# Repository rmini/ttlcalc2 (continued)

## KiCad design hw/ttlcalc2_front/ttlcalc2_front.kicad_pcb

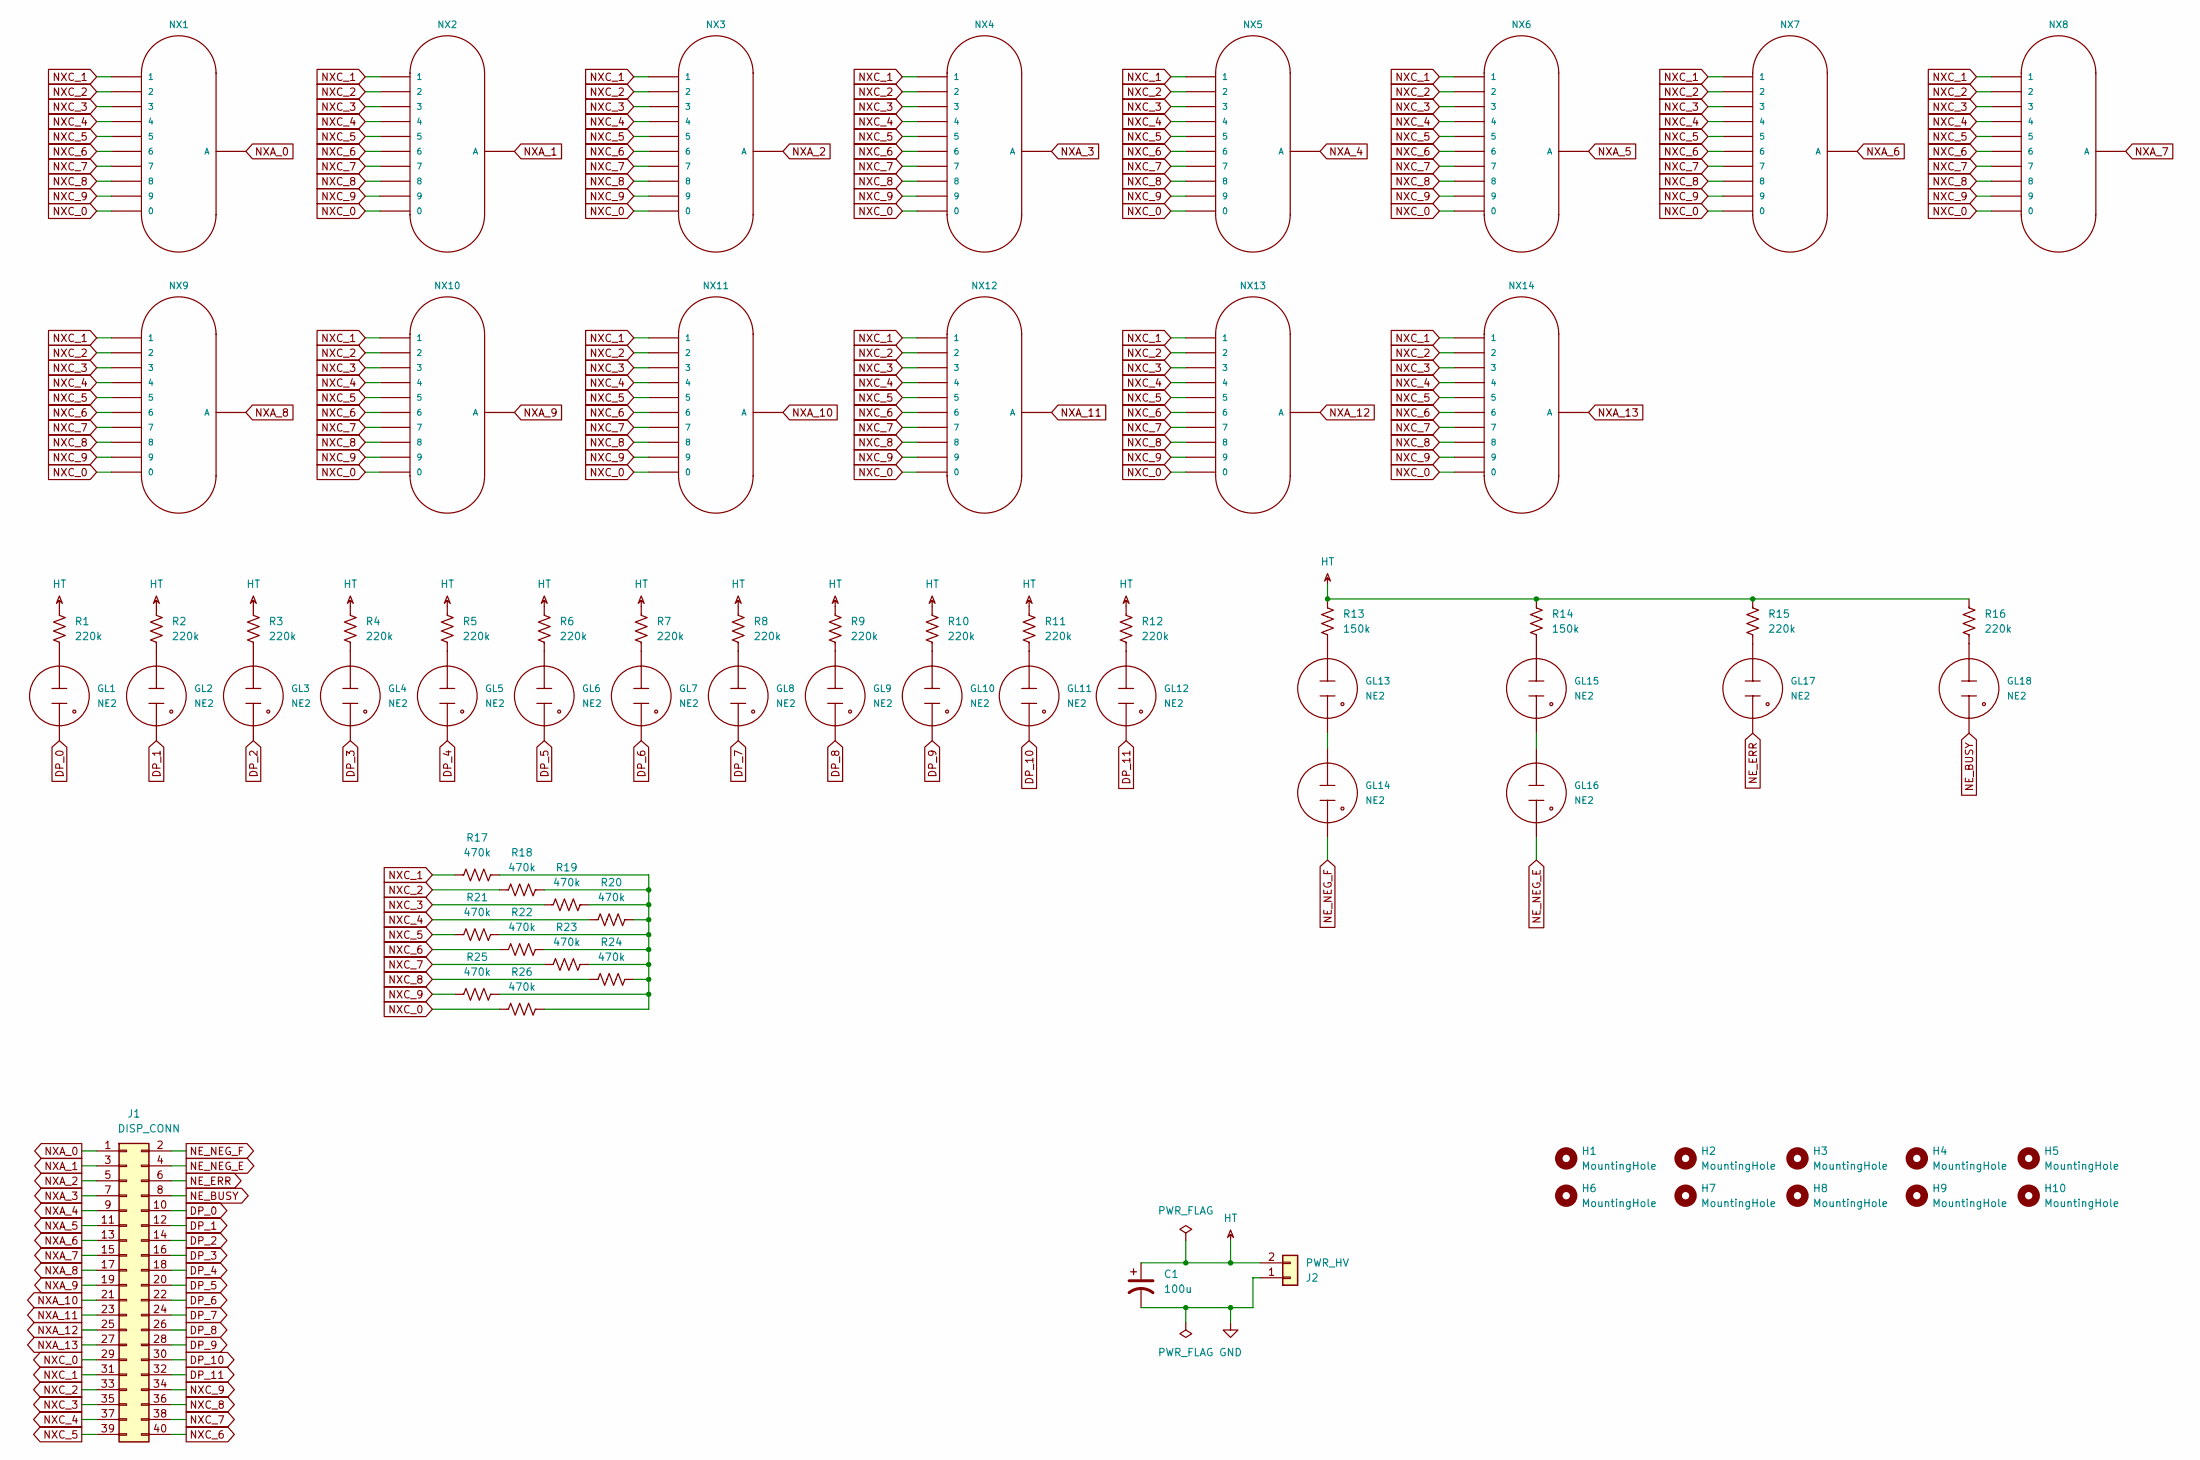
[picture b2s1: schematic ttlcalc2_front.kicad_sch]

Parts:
C1: 100u; CP_Radial_D18.0mm_P7.50mm
GL1, GL2, GL3, GL4, GL5, GL6, GL7, GL8, GL9, GL10, GL11, GL12, GL13, GL14, GL15, GL16, GL17, GL18: NE2; mynixies-NE2-NEON-BULB-DRILL
H1, H2, H3, H4, H5, H6, H7, H8, H9, H10: MountingHole; MountingHole_3.2mm_M3
J1: DISP_CONN; IDC-Header_2x20_P2.54mm_Vertical
J2: PWR_HV; TerminalBlock_Phoenix_MKDS-1,5-2-5.08_1x02_P5.08mm_Horizont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
NX1, NX2, NX3, NX4, NX5, NX6, NX7, NX8, NX9, NX10, NX11, NX12, NX13, NX14: IN-12A; nixies-us-IN-12-DSUB-NOHOLE
R1, R2, R3, R4, R5, R6, R7, R8, R9, R10, R11, R12, R15, R16: 220k; R_Axial_DIN0207_L6.3mm_D2.5mm_P7.62mm_Horizontal
R13, R14: 150k; R_Axial_DIN0207_L6.3mm_D2.5mm_P7.62mm_Horizontal
R17, R18, R19, R20, R21, R22, R23, R24, R25, R26: 470k; R_Axial_DIN0207_L6.3mm_D2.5mm_P7.62mm_Horizontal

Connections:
DP_0: GL1.2 (A1), J1.10
DP_1: GL2.2 (A1), J1.12
DP_2: GL3.2 (A1), J1.14
DP_3: GL4.2 (A1), J1.16
DP_4: GL5.2 (A1), J1.18
DP_5: GL6.2 (A1), J1.20
DP_6: GL7.2 (A1), J1.22
DP_7: GL8.2 (A1), J1.24
DP_8: GL9.2 (A1), J1.26
DP_9: GL10.2 (A1), J1.28
DP_10: GL11.2 (A1), J1.30
DP_11: GL12.2 (A1), J1.32
GND: C1.2, J2.1
HT: C1.1, J2.2, R1.1, R2.1, R3.1, R4.1, R5.1, R6.1, R7.1, R8.1, R9.1, R10.1, R11.1, R12.1, R13.1, R14.1, R15.1, R16.1
NE_BUSY: GL18.2 (A1), J1.8
NE_ERR: GL17.2 (A1), J1.6
NE_NEG_E: GL16.2 (A1), J1.4
NE_NEG_F: GL14.2 (A1), J1.2
NXA_0: J1.1, NX1.A
NXA_1: J1.3, NX2.A
NXA_2: J1.5, NX3.A
NXA_3: J1.7, NX4.A
NXA_4: J1.9, NX5.A
NXA_5: J1.11, NX6.A
NXA_6: J1.13, NX7.A
NXA_7: J1.15, NX8.A
NXA_8: J1.17, NX9.A
NXA_9: J1.19, NX10.A
NXA_10: J1.21, NX11.A
NXA_11: J1.23, NX12.A
NXA_12: J1.25, NX13.A
NXA_13: J1.27, NX14.A
NXC_0: J1.29, NX1.0, NX2.0, NX3.0, NX4.0, NX5.0, NX6.0, NX7.0, NX8.0, NX9.0, NX10.0, NX11.0, NX12.0, NX13.0, NX14.0, R26.1
NXC_1: J1.31, NX1.1, NX2.1, NX3.1, NX4.1, NX5.1, NX6.1, NX7.1, NX8.1, NX9.1, NX10.1, NX11.1, NX12.1, NX13.1, NX14.1, R17.1
NXC_2: J1.33, NX1.2, NX2.2, NX3.2, NX4.2, NX5.2, NX6.2, NX7.2, NX8.2, NX9.2, NX10.2, NX11.2, NX12.2, NX13.2, NX14.2, R18.1
NXC_3: J1.35, NX1.3, NX2.3, NX3.3, NX4.3, NX5.3, NX6.3, NX7.3, NX8.3, NX9.3, NX10.3, NX11.3, NX12.3, NX13.3, NX14.3, R19.1
NXC_4: J1.37, NX1.4, NX2.4, NX3.4, NX4.4, NX5.4, NX6.4, NX7.4, NX8.4, NX9.4, NX10.4, NX11.4, NX12.4, NX13.4, NX14.4, R20.1
NXC_5: J1.39, NX1.5, NX2.5, NX3.5, NX4.5, NX5.5, NX6.5, NX7.5, NX8.5, NX9.5, NX10.5, NX11.5, NX12.5, NX13.5, NX14.5, R21.1
NXC_6: J1.40, NX1.6, NX2.6, NX3.6, NX4.6, NX5.6, NX6.6, NX7.6, NX8.6, NX9.6, NX10.6, NX11.6, NX12.6, NX13.6, NX14.6, R22.1
NXC_7: J1.38, NX1.7, NX2.7, NX3.7, NX4.7, NX5.7, NX6.7, NX7.7, NX8.7, NX9.7, NX10.7, NX11.7, NX12.7, NX13.7, NX14.7, R23.1
NXC_8: J1.36, NX1.8, NX2.8, NX3.8, NX4.8, NX5.8, NX6.8, NX7.8, NX8.8, NX9.8, NX10.8, NX11.8, NX12.8, NX13.8, NX14.8, R24.1
NXC_9: J1.34, NX1.9, NX2.9, NX3.9, NX4.9, NX5.9, NX6.9, NX7.9, NX8.9, NX9.9, NX10.9, NX11.9, NX12.9, NX13.9, NX14.9, R25.1
unnamed: GL1.1 (A), R1.2
unnamed: GL2.1 (A), R2.2
unnamed: GL3.1 (A), R3.2
unnamed: GL4.1 (A), R4.2
unnamed: GL5.1 (A), R5.2
unnamed: GL6.1 (A), R6.2
unnamed: GL7.1 (A), R7.2
unnamed: GL8.1 (A), R8.2
unnamed: GL9.1 (A), R9.2
unnamed: GL10.1 (A), R10.2
unnamed: GL11.1 (A), R11.2
unnamed: GL12.1 (A), R12.2
unnamed: GL13.2 (A1), GL14.1 (A)
unnamed: GL13.1 (A), R13.2
unnamed: GL15.2 (A1), GL16.1 (A)
unnamed: GL15.1 (A), R14.2
unnamed: GL17.1 (A), R15.2
unnamed: GL18.1 (A), R16.2
unnamed: R17.2, R18.2, R19.2, R20.2, R21.2, R22.2, R23.2, R24.2, R25.2, R26.2

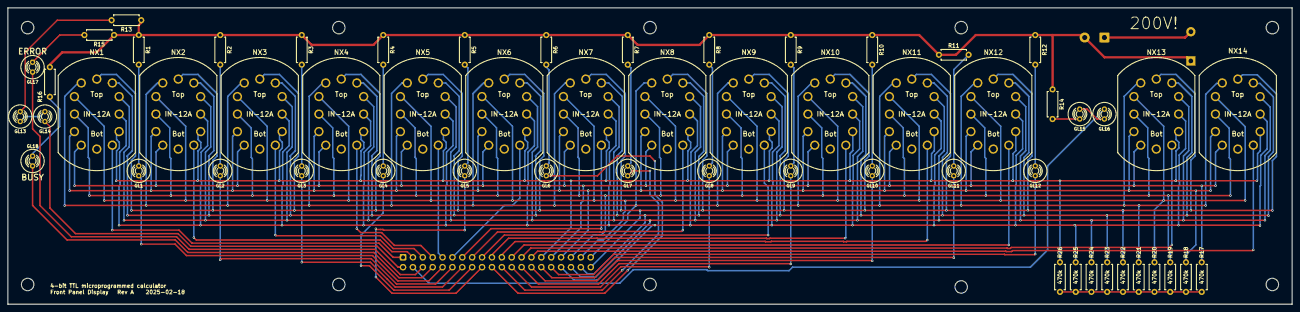
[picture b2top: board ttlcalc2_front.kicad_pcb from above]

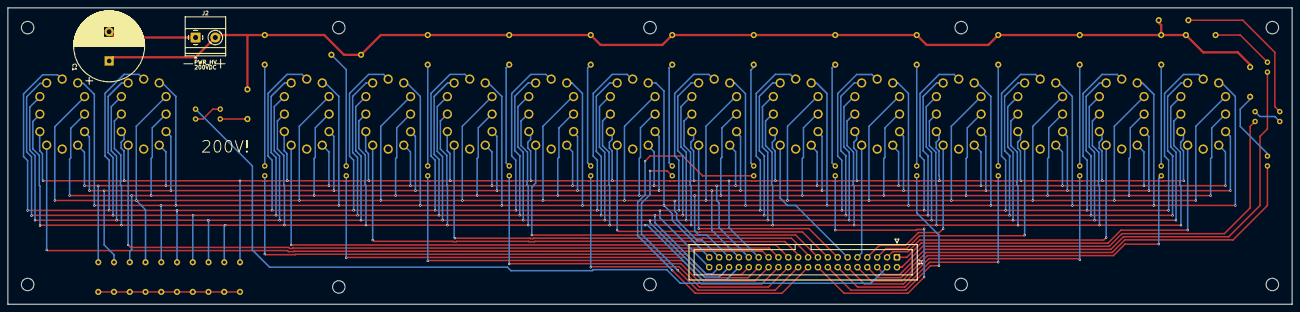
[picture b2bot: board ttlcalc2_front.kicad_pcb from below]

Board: 2 copper layers, 330.2 x 76.2 mm, 71 parts (3 on the bottom side), 61 nets.

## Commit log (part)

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2025-02-13 PCB cleanup
    Swap location of I/O output register and address latch
    Clean up routing
    Via stitch around clock traces
    Fill out sheet description block
2025-02-13 Moved logic board files into subdirectory
2025-02-13 Add in-progress display schematic
2025-02-14 Memory and I/O timing improvements
    Changed memory /WE to use combination of /CLK2 and /WMem to ensure /WE is de-asserted well before memory address becomes invalid
    Removed memory data input register, made unnecessary by above change
    Changed I/O output register to buffer (same reasons above)
    Fixed and updated date on PCB silkscreen
2025-02-15 Continue work on display driver board schematic
2025-02-16 Simplify display driver board, add busy light
    Removed digit storage and multiplexing logic from display driver, will handle in software instead
    Add driver for busy indicator
2025-02-16 Minor simplifications and ERC fix
    Fix missing NE_BUSY from bus definition
    Switch 74LS139 to 74LS138
    Remove extra bypass caps
2025-02-18 Display driver board routing and silkscreen tweaks
2025-02-18 Display driver geographical reannotate
2025-02-19 Commit front panel display board schematic and PCB
2025-02-19 Minor routing tweaks to front panel display
2025-02-24 Convert to KiCad 9.0
    Convert to KiCad 9.0 format
    Tweak silkscreen to fix DRC errors introduced by updated footprints
2025-02-27 Minor display hardware revisions
    Add anti-ghosting inter-cathode resistors to nixies
    Adjust component values based on experiments
    Change from individual netclass labels to rule areas
    Tweak traces on display board
    Update .gitignore to ignore KiCad lock files
2025-02-27 Simulator: Initial revision
2025-02-27 Simulator: More unit testing, bug fixes, etc.
2025-02-28 More resistor value updates, ERC fixes
    Update Nixie anode resistors to 22k based on calculation and experimental verification
    Fix ERC errors due to remaining Logic netclass labels in decimal point sheet
2025-03-01 Simulator: Add Disassemble to Operation class
2025-03-01 Simulator: Implement I/O, Operation fixes and tests
2025-03-03 Simulator: Add tests, abstract memory, refactor
    Add a few tests to get to 100% branch coverage
    Abstract memory to a separate class with overridable read/write operations
    Refactor to reduce complexity
2025-03-04 Simulator: Console UI
2025-03-04 Simulator: Eliminate warnings
2025-03-05 Simulator: Fix UI bugs
2025-03-05 Simulator: Change binaries to big-endian
2025-03-05 Simulator: Add hex to program view
2025-03-05 Simulator: Tweak disassembly format
2025-03-05 Software: Add customasm assembly files
2025-03-06 Simulator: Fix failing unit tests after change to big-endian
2025-03-07 Add README.md for TtlCalc2 project overview and documentation
2025-03-07 Create LICENSE
2025-03-08 Software: Add unary opcodes, optimize fib.asm
2025-03-08 Add documentation
2025-03-10 README: Add links, PCB renders
2025-03-10 README: Add missing links under Simulation section
2025-03-13 Software: Fix mov from y and add assertions - unaryyop definition had typo - added assertions to check for parameter conflicts
